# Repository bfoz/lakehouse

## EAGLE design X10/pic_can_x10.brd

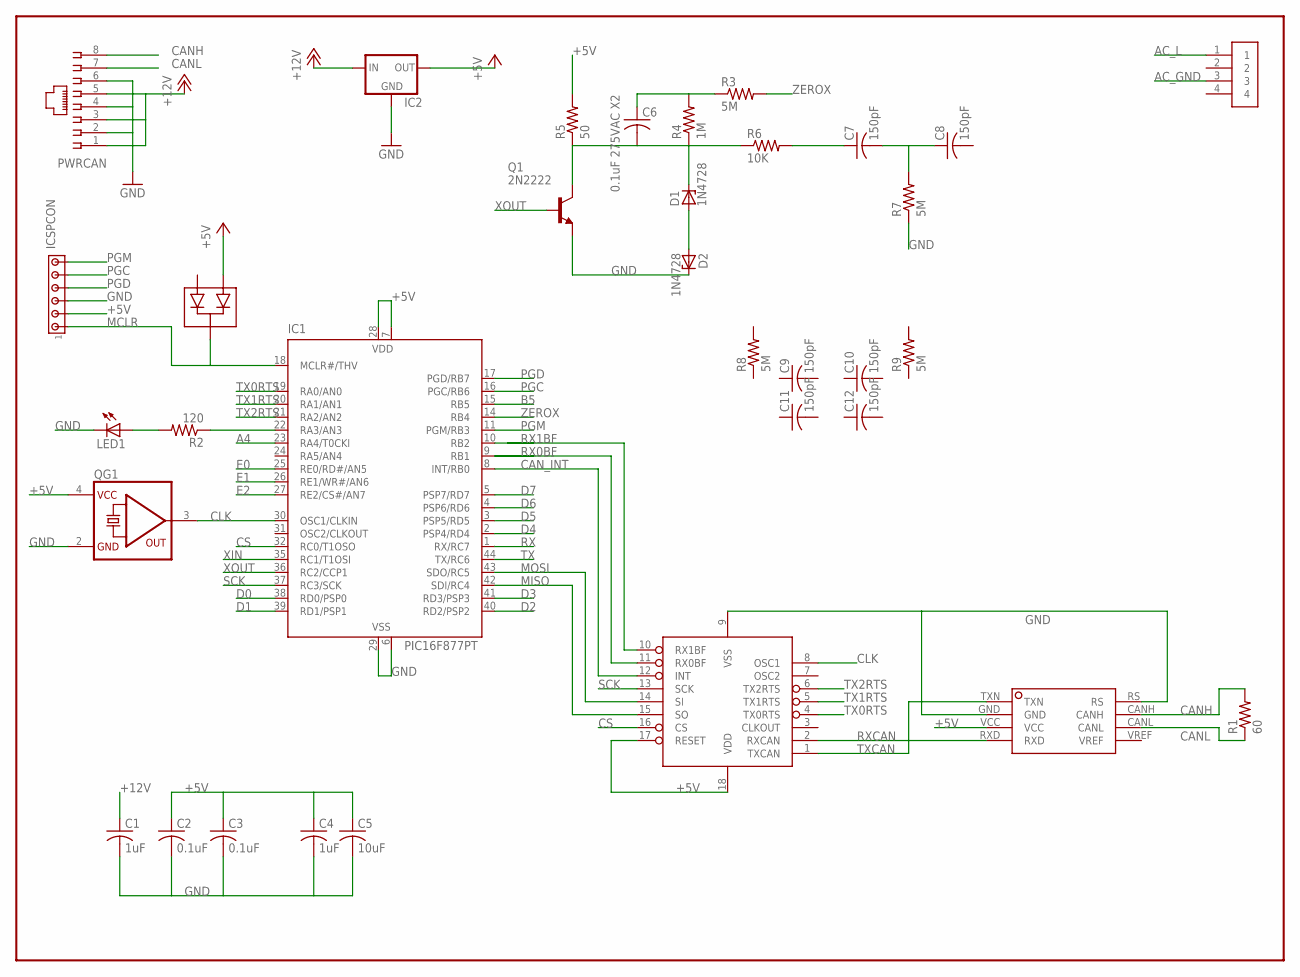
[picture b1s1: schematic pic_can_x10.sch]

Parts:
C1, C4: 1uF; C0805
C2, C3: 0.1uF; C0805
C5: 10uF; C1206
C6: 0.1uF 275VAC X2; C0805
C7, C8, C9, C10, C11, C12: 150pF; C0805
D1, D2: 1N4728; DO41Z10
IC1: PIC16F877PT; TQFP44
IC2: 78XXL
IC3: UC5350D; SOIC8
ICSPCON: MTA06-100; 10X06MTA
LED1: LEDCHIPLED_0805; CHIPLED_0805
MCP1: MCP2510-I/SO; SO-18W
PWRCAN: 555166-1
Q1: 2N2222; TO18
QG1: SG531; DIL08-4
R1: 60; R0805
R2: 120; R0805
R3, R7, R8, R9: 5M; R0805
R4: 1M; R0805
R5: 50; R0805
R6: 10K; R0805
U$1: MPT0.5/4-2.54"; MPT0.5/4-2.54
U$2: BAV70_; SOT-23

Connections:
+5V: C2.1, C3.1, C4.1, C5.1, IC1.7 (VDD), IC1.28 (VDD), IC2.OUT, IC3.VCC, ICSPCON.5 (2), MCP1.17 (RESET), MCP1.18 (VDD), QG1.4 (VCC), R5.2, U$2.1 (A1)
+12V: C1.1, IC2.IN, PWRCAN.1, PWRCAN.3, PWRCAN.5
A4: IC1.23 (RA4/T0CKI)
AC_GND: U$1.3
AC_L: C6.1, R3.1, R4.2, U$1.1
B5: IC1.15 (RB5)
CANH: IC3.CANH, PWRCAN.8, R1.2
CANL: IC3.CANL, PWRCAN.7, R1.1
CAN_INT: IC1.8 (INT/RB0), MCP1.12 (INT)
CLK: IC1.30 (OSC1/CLKIN), MCP1.8 (OSC1), QG1.3 (OUT)
CS: IC1.32 (RC0/T1OSO), MCP1.16 (CS)
D0: IC1.38 (RD0/PSP0)
D1: IC1.39 (RD1/PSP1)
D2: IC1.40 (RD2/PSP2)
D3: IC1.41 (RD3/PSP3)
D4: IC1.2 (PSP4/RD4)
D5: IC1.3 (PSP5/RD5)
D6: IC1.4 (PSP6/RD6)
D7: IC1.5 (PSP7/RD7)
E0: IC1.25 (RE0/RD#/AN5)
E1: IC1.26 (RE1/WR#/AN6)
E2: IC1.27 (RE2/CS#/AN7)
GND: C1.2, C2.2, C3.2, C4.2, C5.2, D2.C, IC1.6 (VSS), IC1.29 (VSS), IC2.GND, IC3.GND, IC3.RS, ICSPCON.4 (3), LED1.C, MCP1.9 (VSS), PWRCAN.2, PWRCAN.4, PWRCAN.6, Q1.1 (E), QG1.2 (GND), R7.1
MCLR: IC1.18 (MCLR#/THV), ICSPCON.6 (1), U$2.3 (C)
MISO: IC1.42 (SDI/RC4), MCP1.15 (SO)
MOSI: IC1.43 (SDO/RC5), MCP1.14 (SI)
unnamed: LED1.A, R2.2
unnamed: C6.2, D1.C, Q1.3 (C), R4.1, R5.1, R6.1
unnamed: IC1.22 (RA3/AN3), R2.1
unnamed: C7.1, R6.2
unnamed: D1.A, D2.A
unnamed: C7.2, C8.1, R7.2
PGC: IC1.16 (PGC/RB6), ICSPCON.2 (5)
PGD: IC1.17 (PGD/RB7), ICSPCON.3 (4)
PGM: IC1.11 (PGM/RB3), ICSPCON.1 (6)
RX: IC1.1 (RX/RC7)
RX0BF: IC1.9 (RB1), MCP1.11 (RX0BF)
RX1BF: IC1.10 (RB2), MCP1.10 (RX1BF)
RXCAN: IC3.RXD, MCP1.2 (RXCAN)
SCK: IC1.37 (RC3/SCK), MCP1.13 (SCK)
TX: IC1.44 (TX/RC6)
TX0RTS: IC1.19 (RA0/AN0), MCP1.4 (TX0RTS)
TX1RTS: IC1.20 (RA1/AN1), MCP1.5 (TX1RTS)
TX2RTS: IC1.21 (RA2/AN2), MCP1.6 (TX2RTS)
TXCAN: IC3.TXN, MCP1.1 (TXCAN)
XIN: IC1.35 (RC1/T1OSI)
XOUT: IC1.36 (RC2/CCP1), Q1.2 (B)
ZEROX: IC1.14 (RB4), R3.2

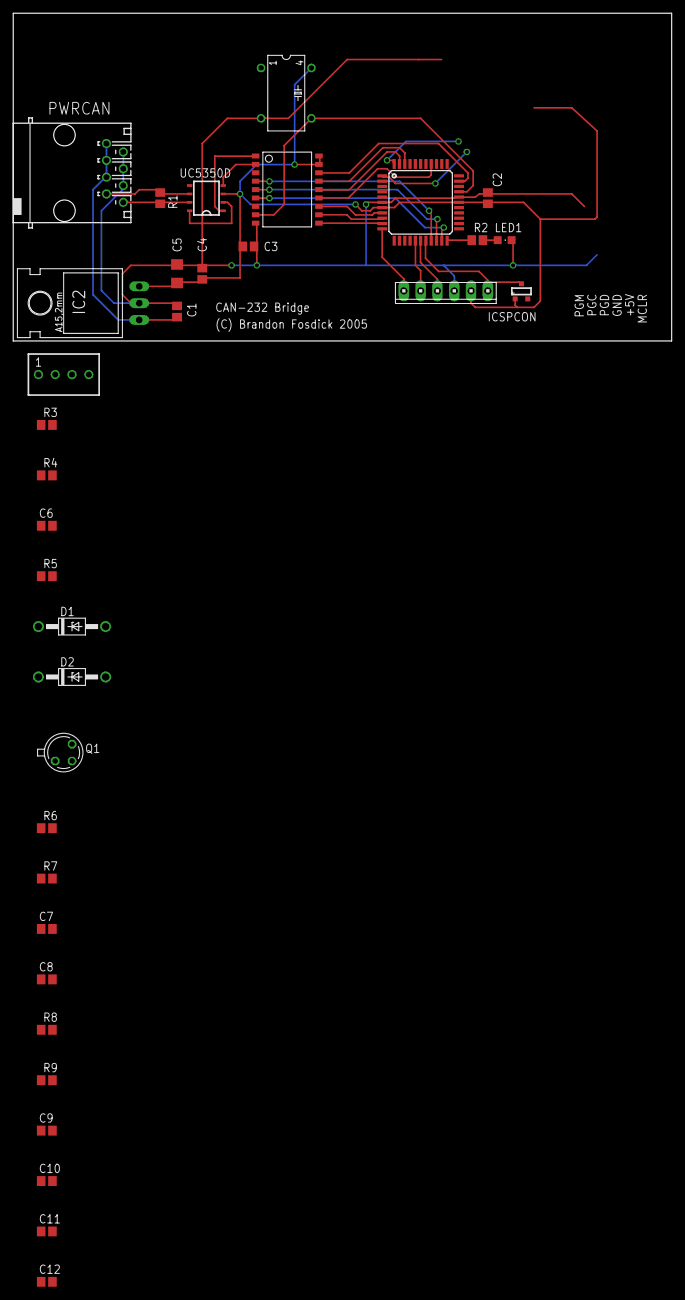
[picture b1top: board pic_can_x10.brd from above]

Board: 2 copper layers, 99.5 x 49.5 mm, 34 parts (0 on the bottom side), 31 nets.

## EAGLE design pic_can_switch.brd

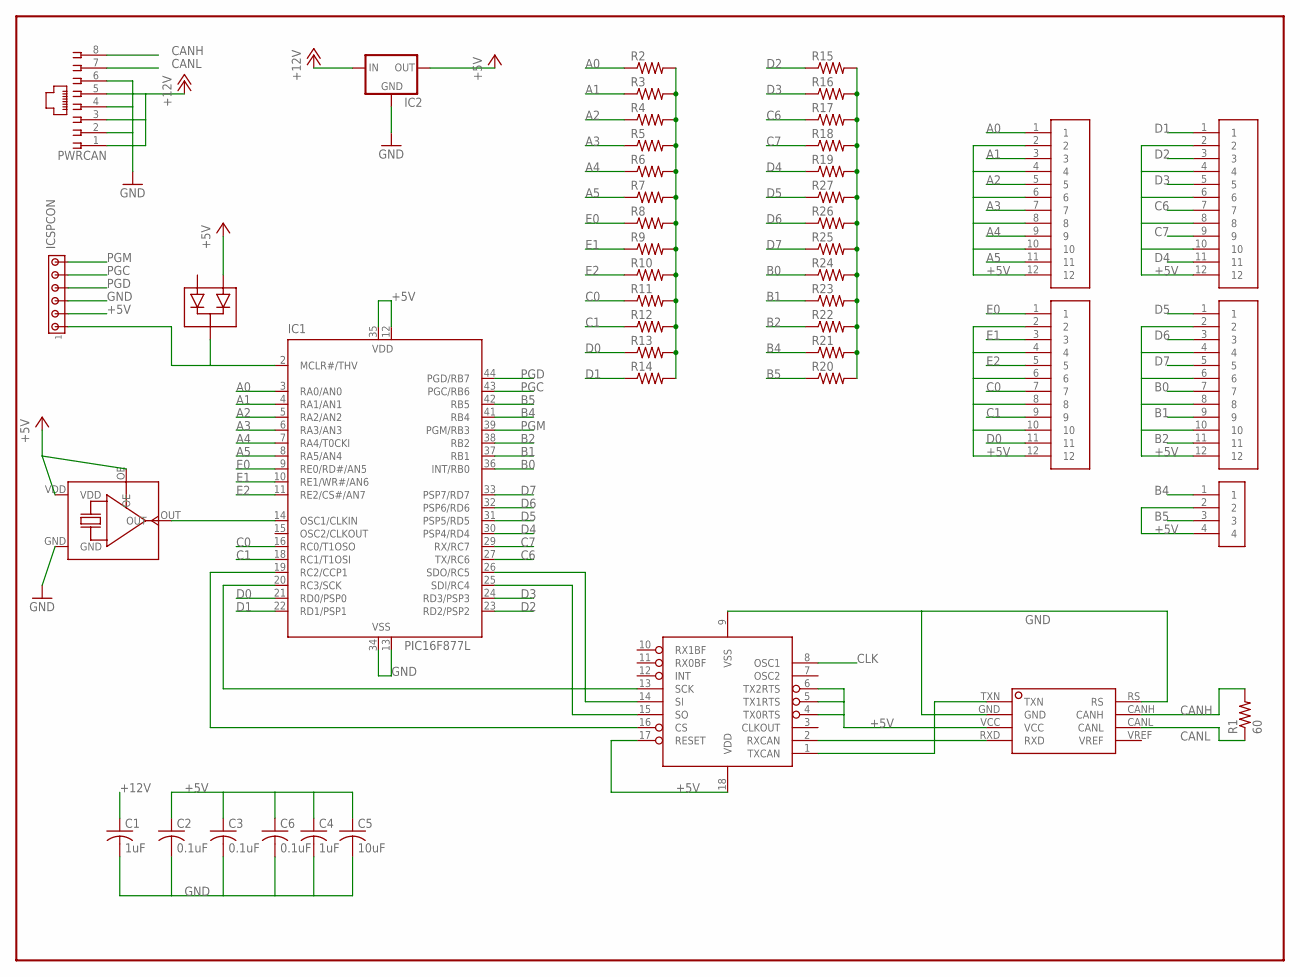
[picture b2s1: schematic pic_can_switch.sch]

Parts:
C1, C4: 1uF; C1206
C2, C3, C6: 0.1uF; C0805
C5: 10uF; C1210
IC1: PIC16F877L; PLCC-44
IC2: 78XXL
IC3: UC5350D; SOIC8
ICSPCON: MTA06-100; 10X06MTA
MCP1: MCP2510-I/SO; SO-18W
PWRCAN: 555764-1
R1: 60; R0805
R2, R3, R4, R5, R6, R7, R8, R9, R10, R11, R12, R13, R14, R15, R16, R17, R18, R19, R20, R21, R22, R23, R24, R25, R26, R27: R-US_R0805; R0805
TB1, TB2, TB3, TB4: MPT0.5/12-2.54
TB5: MPT0.5/4-2.54"; MPT0.5/4-2.54
U$1: SG-615P; SG-615
U$2: BAV70_; SOT-23

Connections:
+5V: C2.1, C3.1, C4.1, C5.1, C6.1, IC1.12 (VDD), IC1.35 (VDD), IC2.OUT, IC3.VCC, ICSPCON.5 (2), MCP1.4 (TX0RTS), MCP1.5 (TX1RTS), MCP1.6 (TX2RTS), MCP1.17 (RESET), MCP1.18 (VDD), TB1.2, TB1.4, TB1.6, TB1.8, TB1.10, TB1.12, TB2.2, TB2.4, TB2.6, TB2.8, TB2.10, TB2.12, TB3.2, TB3.4, TB3.6, TB3.8, TB3.10, TB3.12, TB4.2, TB4.4, TB4.6, TB4.8, TB4.10, TB4.12, TB5.2, TB5.4, U$1.OE, U$1.VDD, U$2.1 (A1)
+12V: C1.1, IC2.IN, PWRCAN.1, PWRCAN.3, PWRCAN.5
A0: IC1.3 (RA0/AN0), R2.1, TB1.1
A1: IC1.4 (RA1/AN1), R3.1, TB1.3
A2: IC1.5 (RA2/AN2), R4.1, TB1.5
A3: IC1.6 (RA3/AN3), R5.1, TB1.7
A4: IC1.7 (RA4/T0CKI), R6.1, TB1.9
A5: IC1.8 (RA5/AN4), R7.1, TB1.11
B0: IC1.36 (INT/RB0), R24.1, TB4.7
B1: IC1.37 (RB1), R23.1, TB4.9
B2: IC1.38 (RB2), R22.1, TB4.11
B4: IC1.41 (RB4), R21.1, TB5.1
B5: IC1.42 (RB5), R20.1, TB5.3
C0: IC1.16 (RC0/T1OSO), R11.1, TB2.7
C1: IC1.18 (RC1/T1OSI), R12.1, TB2.9
C6: IC1.27 (TX/RC6), R17.1, TB3.7
C7: IC1.29 (RX/RC7), R18.1, TB3.9
CANH: IC3.CANH, PWRCAN.8, R1.2
CANL: IC3.CANL, PWRCAN.7, R1.1
CLK: IC1.14 (OSC1/CLKIN), MCP1.8 (OSC1), U$1.OUT
D0: IC1.21 (RD0/PSP0), R13.1, TB2.11
D1: IC1.22 (RD1/PSP1), R14.1, TB3.1
D2: IC1.23 (RD2/PSP2), R15.1, TB3.3
D3: IC1.24 (RD3/PSP3), R16.1, TB3.5
D4: IC1.30 (PSP4/RD4), R19.1, TB3.11
D5: IC1.31 (PSP5/RD5), R27.1, TB4.1
D6: IC1.32 (PSP6/RD6), R26.1, TB4.3
D7: IC1.33 (PSP7/RD7), R25.1, TB4.5
E0: IC1.9 (RE0/RD#/AN5), R8.1, TB2.1
E1: IC1.10 (RE1/WR#/AN6), R9.1, TB2.3
E2: IC1.11 (RE2/CS#/AN7), R10.1, TB2.5
GND: C1.2, C2.2, C3.2, C4.2, C5.2, C6.2, IC1.13 (VSS), IC1.34 (VSS), IC2.GND, IC3.GND, IC3.RS, ICSPCON.4 (3), MCP1.9 (VSS), PWRCAN.2, PWRCAN.4, PWRCAN.6, R2.2, R3.2, R4.2, R5.2, R6.2, R7.2, R8.2, R9.2, R10.2, R11.2, R12.2, R13.2, R14.2, R15.2, R16.2, R17.2, R18.2, R19.2, R20.2, R21.2, R22.2, R23.2, R24.2, R25.2, R26.2, R27.2, U$1.GND
unnamed: IC1.25 (SDI/RC4), MCP1.15 (SO)
unnamed: IC1.26 (SDO/RC5), MCP1.14 (SI)
unnamed: IC1.20 (RC3/SCK), MCP1.13 (SCK)
unnamed: IC1.2 (MCLR#/THV), ICSPCON.6 (1), U$2.3 (C)
unnamed: IC3.TXN, MCP1.1 (TXCAN)
unnamed: IC3.RXD, MCP1.2 (RXCAN)
unnamed: IC1.19 (RC2/CCP1), MCP1.16 (CS)
PGC: IC1.43 (PGC/RB6), ICSPCON.2 (5)
PGD: IC1.44 (PGD/RB7), ICSPCON.3 (4)
PGM: IC1.39 (PGM/RB3), ICSPCON.1 (6)

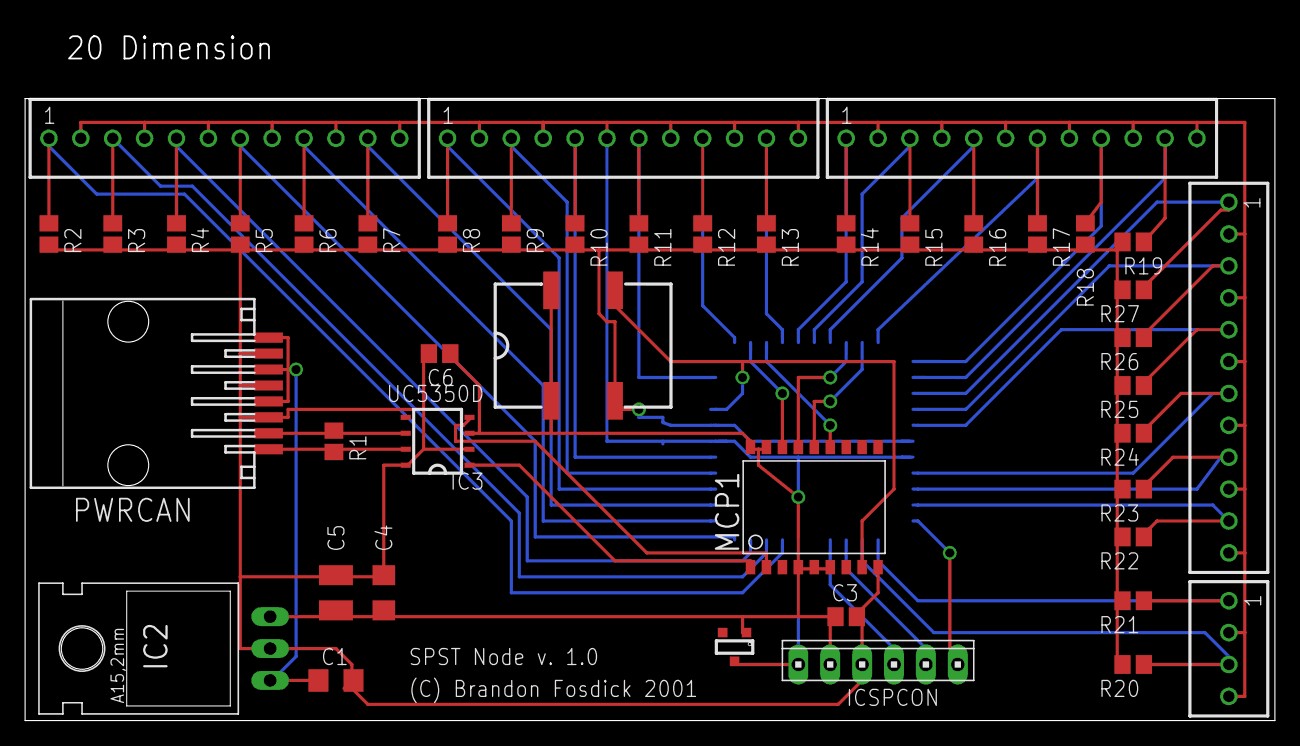
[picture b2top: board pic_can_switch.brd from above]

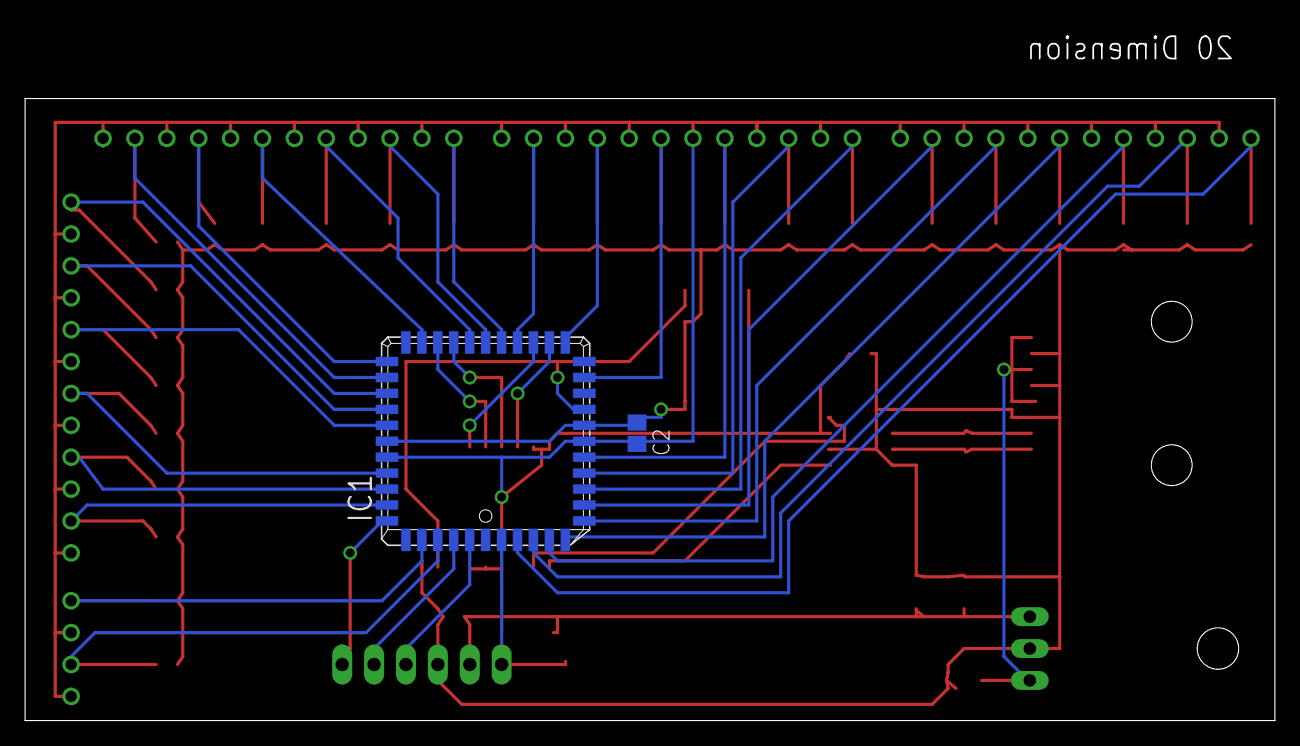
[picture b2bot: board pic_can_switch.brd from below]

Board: 2 copper layers, 99.5 x 49.5 mm, 46 parts (2 on the bottom side), 42 nets.

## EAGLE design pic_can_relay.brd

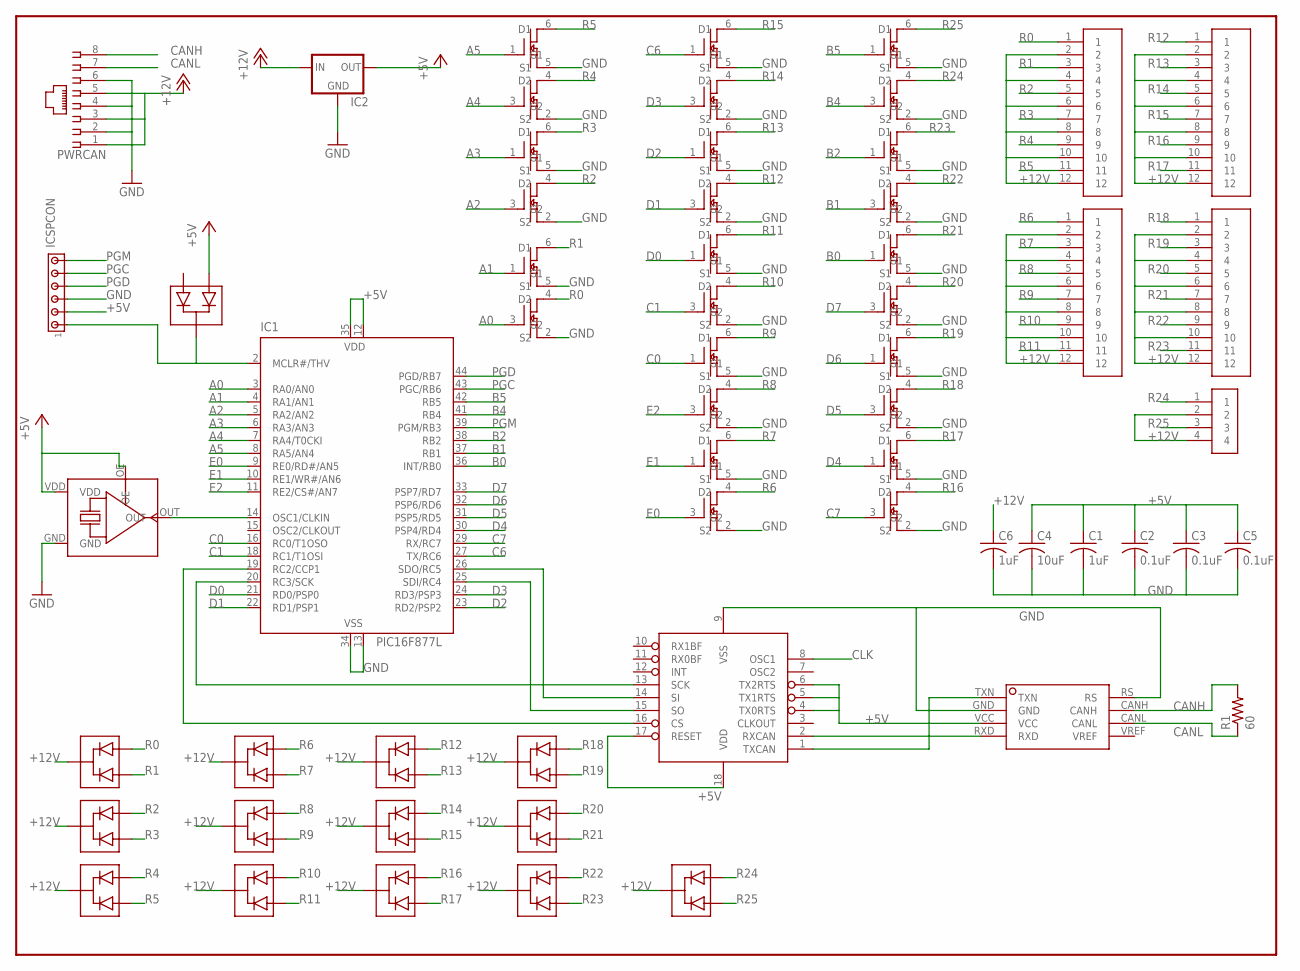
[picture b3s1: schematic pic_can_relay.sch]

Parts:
C1, C6: 1uF; C1206
C2, C3, C5: 0.1uF; C0805
C4: 10uF; C1210
D1, D2, D3, D4, D5, D6, D7, D8, D9, D10, D11, D12, D13, D14: BAV70_; SOT-23
IC1: PIC16F877L; PLCC-44
IC2: 78XXL
IC3: UC5350D; SOIC8
ICSPCON: MTA06-100; 10X06MTA
MCP1: MCP2510-I/SO; SO-18W
PWRCAN: 555764-1
R1: 60; R0805
T1, T2, T3, T4, T5, T6, T7, T8, T9, T10, T11, T12, T13: NDC7002N"; SOT-6
TB1, TB2, TB3, TB4: MPT0.5/12-2.54
TB5: MPT0.5/4-2.54"; MPT0.5/4-2.54
U$1: SG-615P; SG-615

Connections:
+5V: C1.1, C2.1, C3.1, C4.1, C5.1, D1.1 (A1), IC1.12 (VDD), IC1.35 (VDD), IC2.OUT, IC3.VCC, ICSPCON.5 (2), MCP1.4 (TX0RTS), MCP1.5 (TX1RTS), MCP1.6 (TX2RTS), MCP1.17 (RESET), MCP1.18 (VDD), U$1.OE, U$1.VDD
+12V: C6.1, D2.3 (C), D3.3 (C), D4.3 (C), D5.3 (C), D6.3 (C), D7.3 (C), D8.3 (C), D9.3 (C), D10.3 (C), D11.3 (C), D12.3 (C), D13.3 (C), D14.3 (C), IC2.IN, PWRCAN.1, PWRCAN.3, PWRCAN.5, TB1.2, TB1.4, TB1.6, TB1.8, TB1.10, TB1.12, TB2.2, TB2.4, TB2.6, TB2.8, TB2.10, TB2.12, TB3.2, TB3.4, TB3.6, TB3.8, TB3.10, TB3.12, TB4.2, TB4.4, TB4.6, TB4.8, TB4.10, TB4.12, TB5.2, TB5.4
A0: IC1.3 (RA0/AN0), T1.3 (G2)
A1: IC1.4 (RA1/AN1), T1.1 (G1)
A2: IC1.5 (RA2/AN2), T2.3 (G2)
A3: IC1.6 (RA3/AN3), T2.1 (G1)
A4: IC1.7 (RA4/T0CKI), T3.3 (G2)
A5: IC1.8 (RA5/AN4), T3.1 (G1)
B0: IC1.36 (INT/RB0), T11.1 (G1)
B1: IC1.37 (RB1), T12.3 (G2)
B2: IC1.38 (RB2), T12.1 (G1)
B4: IC1.41 (RB4), T13.3 (G2)
B5: IC1.42 (RB5), T13.1 (G1)
C0: IC1.16 (RC0/T1OSO), T5.1 (G1)
C1: IC1.18 (RC1/T1OSI), T6.3 (G2)
C6: IC1.27 (TX/RC6), T8.1 (G1)
C7: IC1.29 (RX/RC7), T9.3 (G2)
CANH: IC3.CANH, PWRCAN.8, R1.2
CANL: IC3.CANL, PWRCAN.7, R1.1
CLK: IC1.14 (OSC1/CLKIN), MCP1.8 (OSC1), U$1.OUT
D0: IC1.21 (RD0/PSP0), T6.1 (G1)
D1: IC1.22 (RD1/PSP1), T7.3 (G2)
D2: IC1.23 (RD2/PSP2), T7.1 (G1)
D3: IC1.24 (RD3/PSP3), T8.3 (G2)
D4: IC1.30 (PSP4/RD4), T9.1 (G1)
D5: IC1.31 (PSP5/RD5), T10.3 (G2)
D6: IC1.32 (PSP6/RD6), T10.1 (G1)
D7: IC1.33 (PSP7/RD7), T11.3 (G2)
E0: IC1.9 (RE0/RD#/AN5), T4.3 (G2)
E1: IC1.10 (RE1/WR#/AN6), T4.1 (G1)
E2: IC1.11 (RE2/CS#/AN7), T5.3 (G2)
GND: C1.2, C2.2, C3.2, C4.2, C5.2, C6.2, IC1.13 (VSS), IC1.34 (VSS), IC2.GND, IC3.GND, IC3.RS, ICSPCON.4 (3), MCP1.9 (VSS), PWRCAN.2, PWRCAN.4, PWRCAN.6, T1.2 (S2), T1.5 (S1), T2.2 (S2), T2.5 (S1), T3.2 (S2), T3.5 (S1), T4.2 (S2), T4.5 (S1), T5.2 (S2), T5.5 (S1), T6.2 (S2), T6.5 (S1), T7.2 (S2), T7.5 (S1), T8.2 (S2), T8.5 (S1), T9.2 (S2), T9.5 (S1), T10.2 (S2), T10.5 (S1), T11.2 (S2), T11.5 (S1), T12.2 (S2), T12.5 (S1), T13.2 (S2), T13.5 (S1), U$1.GND
unnamed: IC1.25 (SDI/RC4), MCP1.15 (SO)
unnamed: IC1.26 (SDO/RC5), MCP1.14 (SI)
unnamed: IC1.20 (RC3/SCK), MCP1.13 (SCK)
unnamed: D1.3 (C), IC1.2 (MCLR#/THV), ICSPCON.6 (1)
unnamed: IC3.TXN, MCP1.1 (TXCAN)
unnamed: IC3.RXD, MCP1.2 (RXCAN)
unnamed: IC1.19 (RC2/CCP1), MCP1.16 (CS)
PGC: IC1.43 (PGC/RB6), ICSPCON.2 (5)
PGD: IC1.44 (PGD/RB7), ICSPCON.3 (4)
PGM: IC1.39 (PGM/RB3), ICSPCON.1 (6)
R0: D2.2 (A2), T1.4 (D2), TB1.1
R1: D2.1 (A1), T1.6 (D1), TB1.3
R2: D3.2 (A2), T2.4 (D2), TB1.5
R3: D3.1 (A1), T2.6 (D1), TB1.7
R4: D4.2 (A2), T3.4 (D2), TB1.9
R5: D4.1 (A1), T3.6 (D1), TB1.11
R6: D5.2 (A2), T4.4 (D2), TB2.1
R7: D5.1 (A1), T4.6 (D1), TB2.3
R8: D6.2 (A2), T5.4 (D2), TB2.5
R9: D6.1 (A1), T5.6 (D1), TB2.7
R10: D7.2 (A2), T6.4 (D2), TB2.9
R11: D7.1 (A1), T6.6 (D1), TB2.11
R12: D8.2 (A2), T7.4 (D2), TB3.1
R13: D8.1 (A1), T7.6 (D1), TB3.3
R14: D9.2 (A2), T8.4 (D2), TB3.5
R15: D9.1 (A1), T8.6 (D1), TB3.7
R16: D10.2 (A2), T9.4 (D2), TB3.9
R17: D10.1 (A1), T9.6 (D1), TB3.11
R18: D11.2 (A2), T10.4 (D2), TB4.1
R19: D11.1 (A1), T10.6 (D1), TB4.3
R20: D12.2 (A2), T11.4 (D2), TB4.5
R21: D12.1 (A1), T11.6 (D1), TB4.7
R22: D13.2 (A2), T12.4 (D2), TB4.9
R23: D13.1 (A1), T12.6 (D1), TB4.11
R24: D14.2 (A2), T13.4 (D2), TB5.1
R25: D14.1 (A1), T13.6 (D1), TB5.3

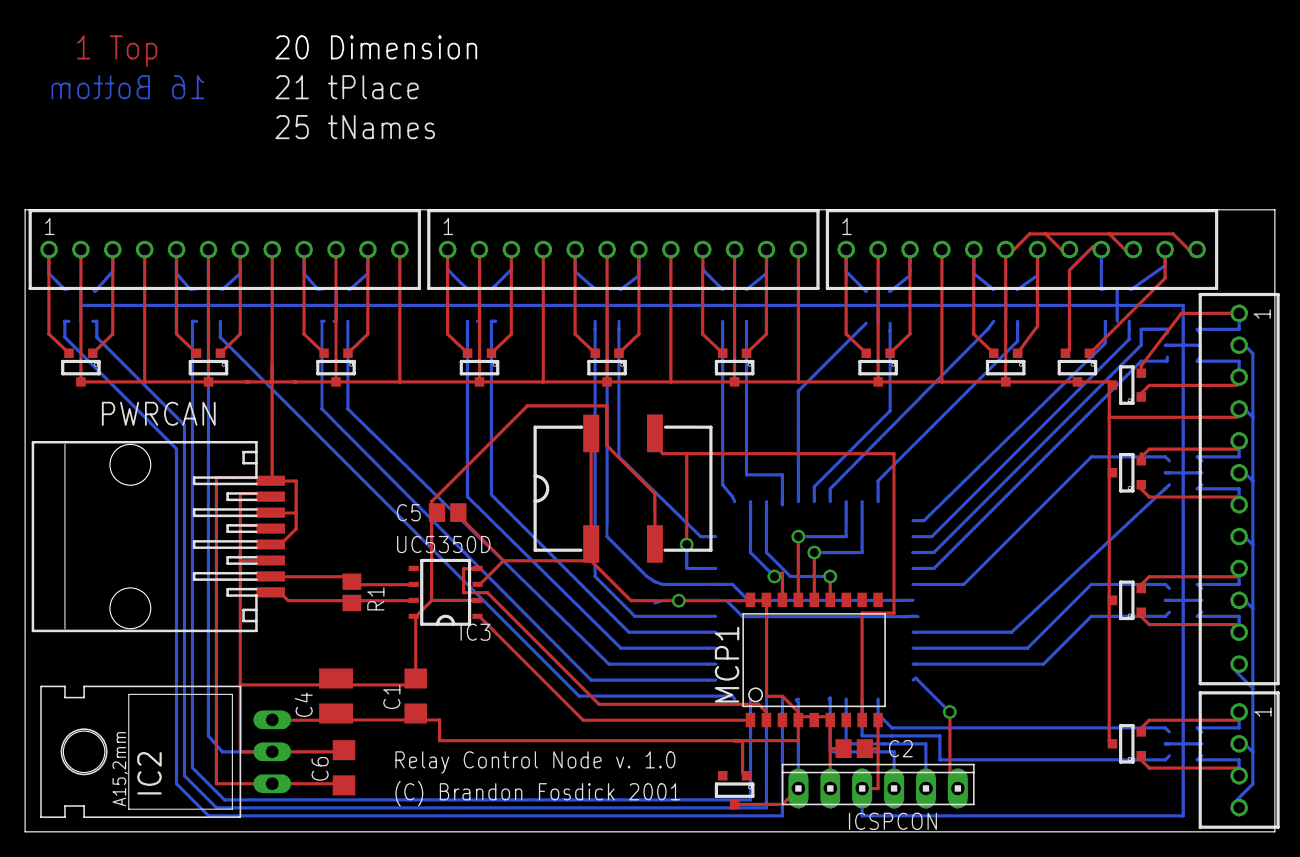
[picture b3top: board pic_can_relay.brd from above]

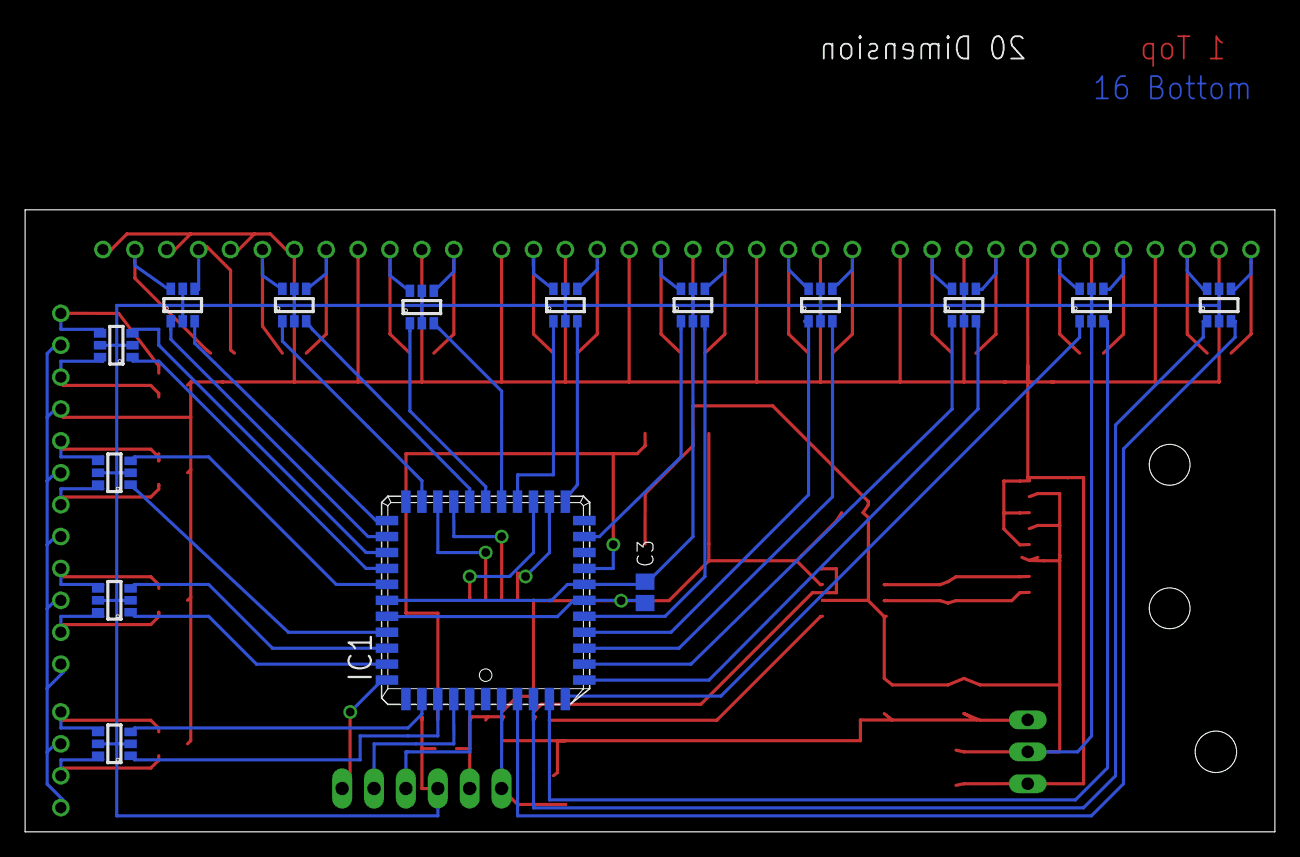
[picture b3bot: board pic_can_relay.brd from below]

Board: 2 copper layers, 99.5 x 49.5 mm, 46 parts (15 on the bottom side), 68 nets.

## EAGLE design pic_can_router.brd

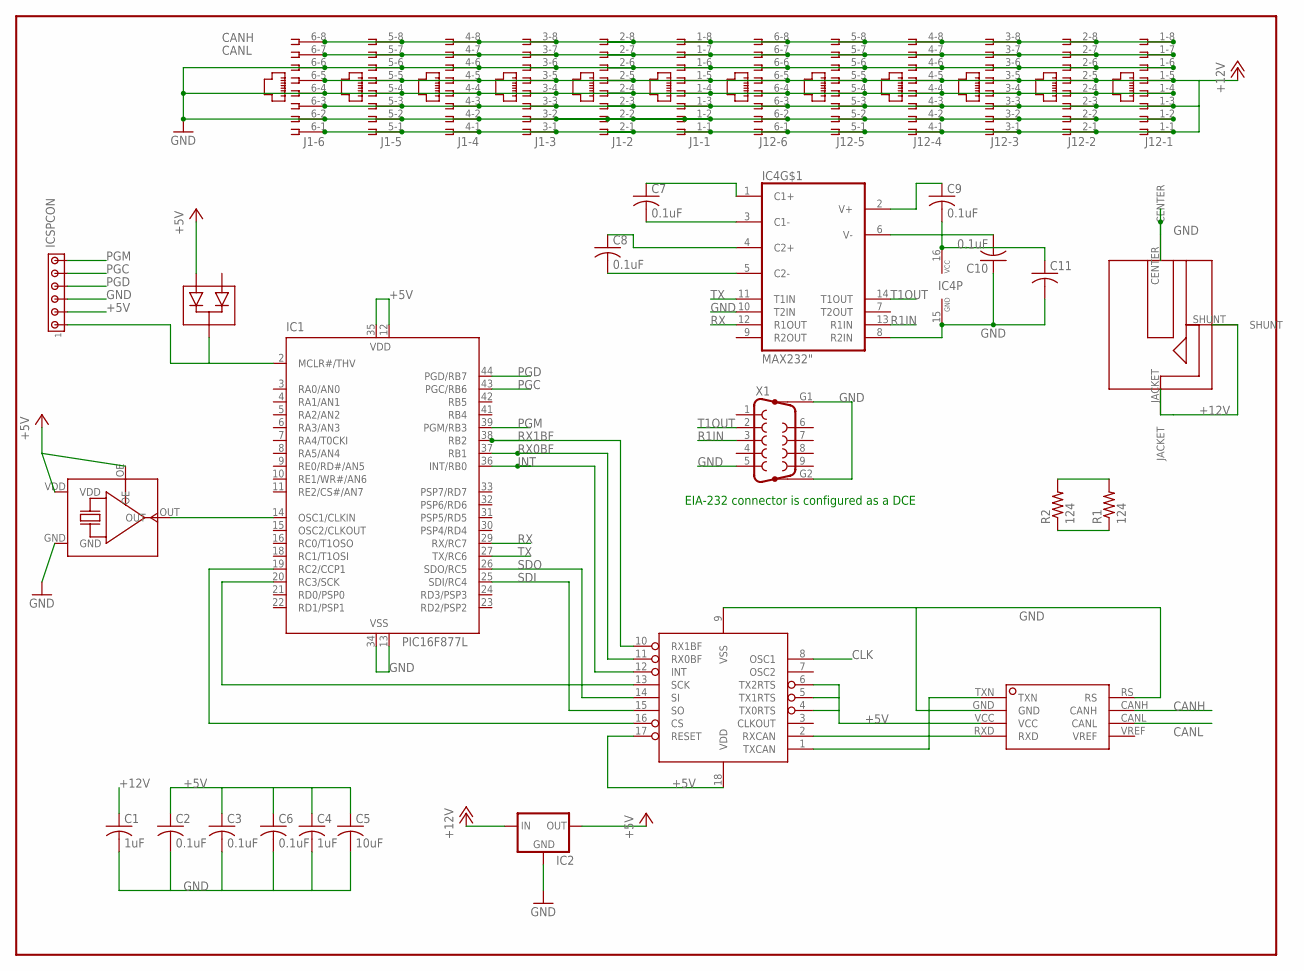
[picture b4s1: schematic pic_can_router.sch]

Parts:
C1, C4: 1uF; C1206
C2, C3, C6, C7, C8, C9, C10: 0.1uF; C0805
C5: 10uF; C1210
C11: C-USC0805; C0805
IC1: PIC16F877L; PLCC-44
IC2: 78XXL
IC3: UC5350D; SOIC8
IC4: MAX232"; SO16
ICSPCON: MTA06-100; 10X06MTA
J1, J12: 557564-1
MCP1: MCP2510-I/SO; SO-18W@1
R1, R2: 124; R0805
U$1: SG-615P; SG-615
U$2: BAV70_; SOT-23
U$3: RAPC712"; RAPC712
X1: F09HP

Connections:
+5V: C2.1, C3.1, C4.1, C5.1, C6.1, C9.2, C11.1, IC1.12 (VDD), IC1.35 (VDD), IC2.OUT, IC3.VCC, IC4.16 (VCC), ICSPCON.5 (2), MCP1.4 (TX0RTS), MCP1.5 (TX1RTS), MCP1.6 (TX2RTS), MCP1.17 (RESET), MCP1.18 (VDD), U$1.OE, U$1.VDD, U$2.2 (A2)
+12V: C1.1, IC2.IN, J1.1-1 (1), J1.1-3 (3), J1.1-5 (5), J1.2-1 (1), J1.2-3 (3), J1.2-5 (5), J1.3-1 (1), J1.3-3 (3), J1.3-5 (5), J1.4-1 (1), J1.4-3 (3), J1.4-5 (5), J1.5-1 (1), J1.5-3 (3), J1.5-5 (5), J1.6-1 (1), J1.6-3 (3), J1.6-5 (5), J12.1-1 (1), J12.1-3 (3), J12.1-5 (5), J12.2-1 (1), J12.2-3 (3), J12.2-5 (5), J12.3-1 (1), J12.3-3 (3), J12.3-5 (5), J12.4-1 (1), J12.4-3 (3), J12.4-5 (5), J12.5-1 (1), J12.5-3 (3), J12.5-5 (5), J12.6-1 (1), J12.6-3 (3), J12.6-5 (5), U$3.JACKET, U$3.SHUNT
CANH: IC3.CANH, J1.1-8 (8), J1.2-8 (8), J1.3-8 (8), J1.4-8 (8), J1.5-8 (8), J1.6-8 (8), J12.1-8 (8), J12.2-8 (8), J12.3-8 (8), J12.4-8 (8), J12.5-8 (8), J12.6-8 (8), R1.2, R2.2
CANL: IC3.CANL, J1.1-7 (7), J1.2-7 (7), J1.3-7 (7), J1.4-7 (7), J1.5-7 (7), J1.6-7 (7), J12.1-7 (7), J12.2-7 (7), J12.3-7 (7), J12.4-7 (7), J12.5-7 (7), J12.6-7 (7), R1.1, R2.1
CLK: IC1.14 (OSC1/CLKIN), MCP1.8 (OSC1), U$1.OUT
CS: IC1.19 (RC2/CCP1), MCP1.16 (CS)
GND: C1.2, C2.2, C3.2, C4.2, C5.2, C6.2, C10.1, C11.2, IC1.13 (VSS), IC1.34 (VSS), IC2.GND, IC3.GND, IC3.RS, IC4.8 (R2IN), IC4.10 (T2IN), IC4.15 (GND), ICSPCON.4 (3), J1.1-2 (2), J1.1-4 (4), J1.1-6 (6), J1.2-2 (2), J1.2-4 (4), J1.2-6 (6), J1.3-2 (2), J1.3-4 (4), J1.3-6 (6), J1.4-2 (2), J1.4-4 (4), J1.4-6 (6), J1.5-2 (2), J1.5-4 (4), J1.5-6 (6), J1.6-2 (2), J1.6-4 (4), J1.6-6 (6), J12.1-2 (2), J12.1-4 (4), J12.1-6 (6), J12.2-2 (2), J12.2-4 (4), J12.2-6 (6), J12.3-2 (2), J12.3-4 (4), J12.3-6 (6), J12.4-2 (2), J12.4-4 (4), J12.4-6 (6), J12.5-2 (2), J12.5-4 (4), J12.5-6 (6), J12.6-2 (2), J12.6-4 (4), J12.6-6 (6), MCP1.9 (VSS), U$1.GND, U$3.CENTER, X1.5, X1.G1, X1.G2
INT: IC1.36 (INT/RB0), MCP1.12 (INT)
unnamed: C7.1, IC4.1 (C1+)
unnamed: C7.2, IC4.3 (C1-)
unnamed: C8.2, IC4.5 (C2-)
unnamed: C8.1, IC4.4 (C2+)
unnamed: IC1.2 (MCLR#/THV), ICSPCON.6 (1), U$2.3 (C)
unnamed: C9.1, IC4.2 (V+)
unnamed: C10.2, IC4.6 (V-)
PGC: IC1.43 (PGC/RB6), ICSPCON.2 (5)
PGD: IC1.44 (PGD/RB7), ICSPCON.3 (4)
PGM: IC1.39 (PGM/RB3), ICSPCON.1 (6)
R1IN: IC4.13 (R1IN), X1.3
RX: IC1.29 (RX/RC7), IC4.12 (R1OUT)
RX0BF: IC1.37 (RB1), MCP1.11 (RX0BF)
RX1BF: IC1.38 (RB2), MCP1.10 (RX1BF)
RXCAN: IC3.RXD, MCP1.2 (RXCAN)
SCK: IC1.20 (RC3/SCK), MCP1.13 (SCK)
SDI: IC1.25 (SDI/RC4), MCP1.15 (SO)
SDO: IC1.26 (SDO/RC5), MCP1.14 (SI)
T1OUT: IC4.14 (T1OUT), X1.2
TX: IC1.27 (TX/RC6), IC4.11 (T1IN)
TXCAN: IC3.TXN, MCP1.1 (TXCAN)

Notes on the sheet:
EIA-232 connector is configured as a DCE

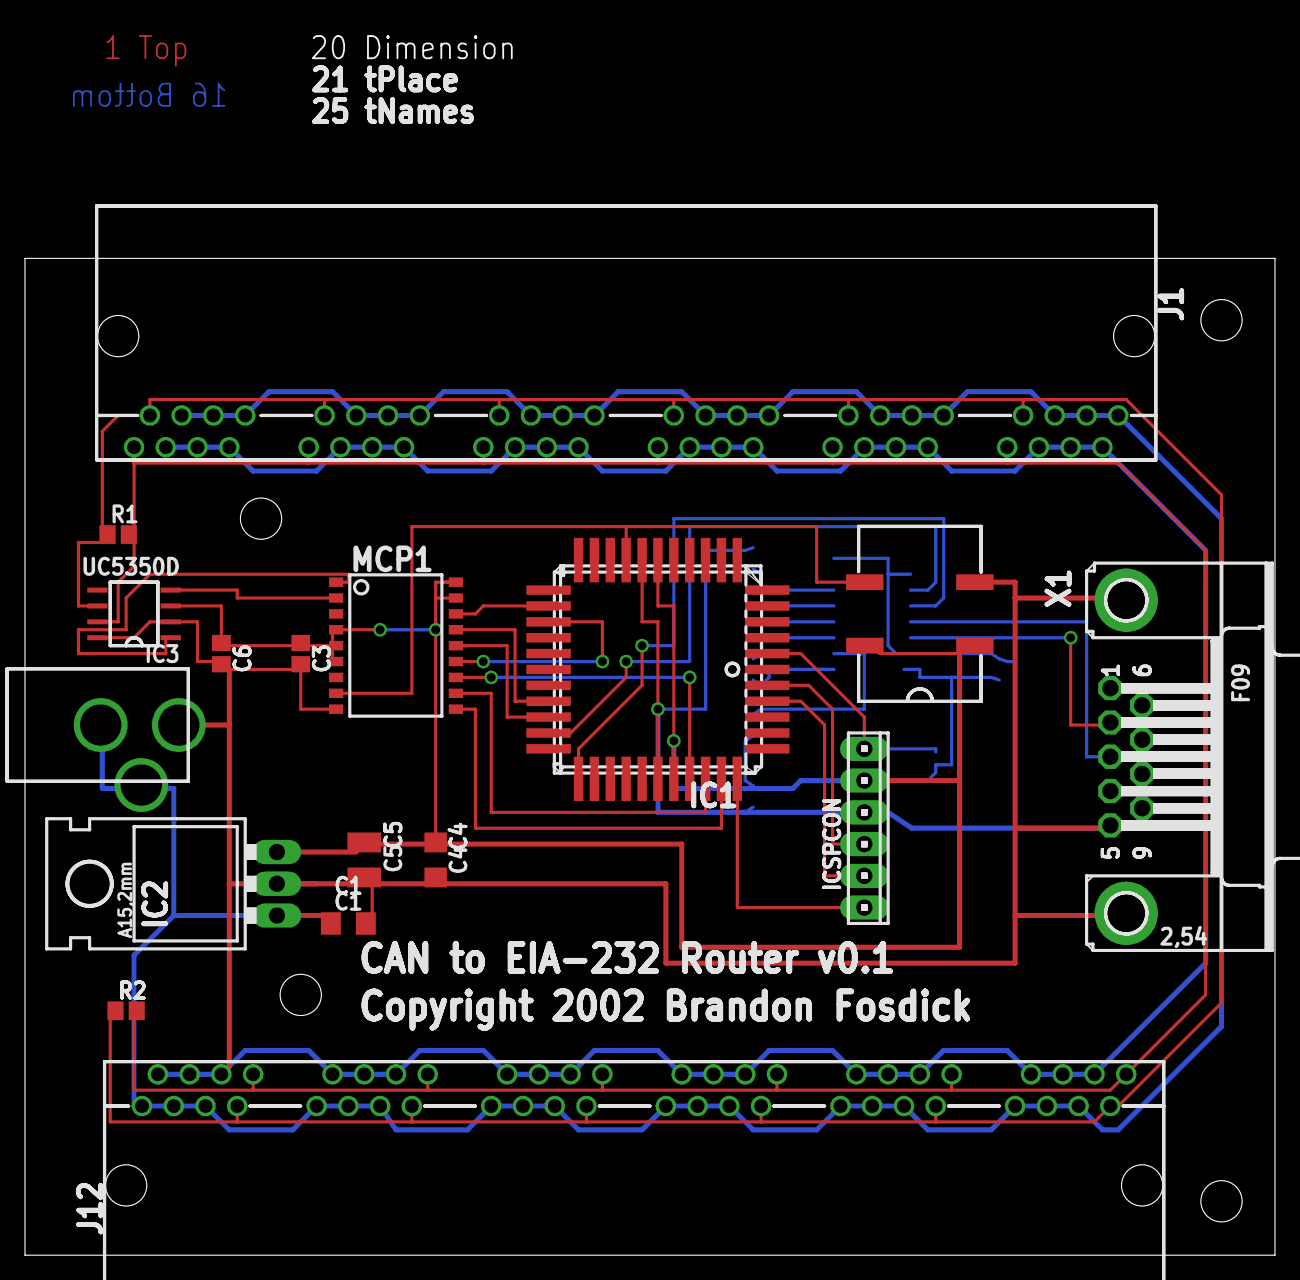
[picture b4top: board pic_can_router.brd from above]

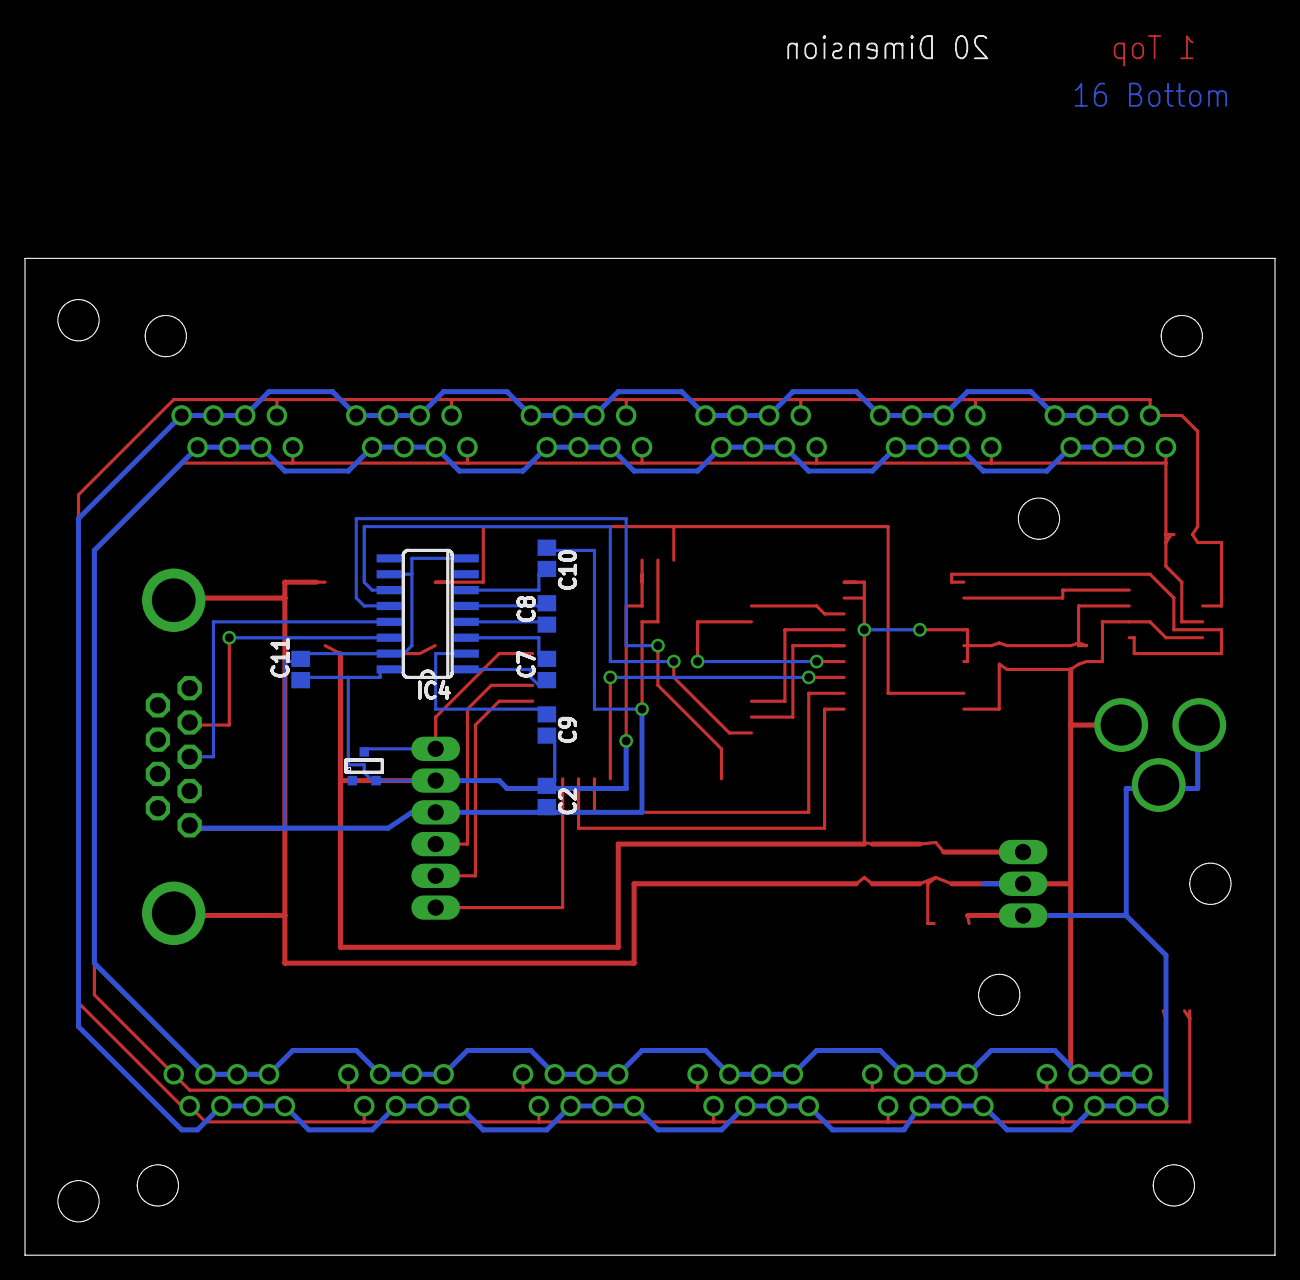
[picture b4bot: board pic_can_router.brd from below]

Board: 2 copper layers, 100.0 x 79.7 mm, 25 parts (8 on the bottom side), 29 nets.

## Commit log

2013-11-08 Imported a very old archive of the house project hardware files
    I'm not sure if this is the original, or if it's merely the earliest version that I still have
2013-11-08 Imported another old copy
    This appears to be a slightly younger version of the hardware files. Apparently I had reorganized things a bit.
2013-11-08 Imported an old web page for the project
    This is from an old backup that contained this file and a zip of the files that becamse the first import commit in this repository. I'm not really sure where it had been hosted.
2013-11-08 Opened the project in Eagle 6.5.0 for Windows
    Allowed it to upgrade all of the files (by opening each file individually)
